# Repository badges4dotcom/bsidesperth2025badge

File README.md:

# BSides Perth 2025 Badge

## Physical Badge

Instructions on how to assemble the physical badge can be found [here](docs/AssemblyInstructions.md)

If a re-download of the physical badge is required, follow these [instructions](docs/DownloadInstructions.md). This will be required if you wish to attempt the online challenges (see Known Issues below).

### Parts List

| Qty | Item | Link | Alternative Link |
| --- | --- | --- | --- |
| 4	| 6x6x6mm Push Button Tactile Switch | [Link](https://a.aliexpress.com/_mtKEuoZ) || 
| 4	| 10k 1/4W 1% Metal Film Resistor | [Link](https://a.aliexpress.com/_m0tmaNF) ||
| 1	| 1x4 2.54mm Male Header Pin Connector | [Link](https://a.aliexpress.com/_mLn1ap7) ||
| 1	| 1x8 2.54mm Female Header Pin Connector | [Link](https://a.aliexpress.com/_mquvebf) | [Link](https://a.aliexpress.com/_mNltGYh) |
| 1	| 1x4 2.54mm Female Header Pin Connector | [Link](https://a.aliexpress.com/_mquvebf) | [Link](https://a.aliexpress.com/_mNltGYh) |
| 2	| 1x15 2.54mm Female Header Pin Connector | [Link](https://a.aliexpress.com/_mquvebf) | [Link](https://a.aliexpress.com/_mNltGYh) |
| 1	| 2x3 2.54mm Femal Header Pin Connector	| [Link](https://a.aliexpress.com/_mK6bxvJ) ||
| 1	| ESP32 DOIT DevKit v1 - 30Pin | [Link](https://a.aliexpress.com/_mr7LSPJ) ||
| 1	| 1.8" LCD TFT Display | [Link](https://a.aliexpress.com/_mPspKyp) ||

## Virtual Badge

The virtual badge can be accessed here: https://badge.bsidesperth.com.au/

The code for the Virtual Badge code can be found in this repository under "VirtualBadge".

The virtual badge does not support "Online Challenges", but does contain hidden features such as a second episode, cheats, and an easter egg.

The virtual badge now supports keyboard inputs. The four buttons are mapped to W [Up], S [Down], A [Left/A], and D [Right/B]. Once a keyboard input is used, the symbols used in the sequence game change to U = UP, D = DOWN, L = LEFT, R = RIGHT. Thanks again to Matt for the suggestion and the code snippet for this feature. 

## Physical Badge Code Template

There is a basic template for an Arduino program under the folder "Template". The template demonstrates basic use of the LCD screen, ESP32, and button inputs. The download instructions can be found [here](docs/DownloadInstructions.md).

## Virtual Badge Server (API for Online Challenges)

Code for the Virtual Badge Server (API for Online Challenges) will be made available ~1st November 2025.

## Badge Holder (3D Print)

A badge holder can be 3D printed using an off-the-shelf 3D printer. Recommended print settings are PLA plastic, 60+% infill, 40mm/s print speed. Some stringing may occur if filament is damp and/or print speed is too high.

## Customisation

Customisation of the virtual and physical badge are both possible. Extra details can be found [here](docs/Customisation.md)

## Known Issues

- To play the Online Challenges on a ESP32 supplied in a component pack, a re-download of the physical badge code to the ESP32 is required. [Fixed]
- Online Challenges were unavailable (18th Oct) due to firewall issue. This has since been resolved. [Fixed]
- Offline Challenges now generates sequences which use all four buttons (only three buttons were being used in the original code). [Fixed]

## Like the game/badge?

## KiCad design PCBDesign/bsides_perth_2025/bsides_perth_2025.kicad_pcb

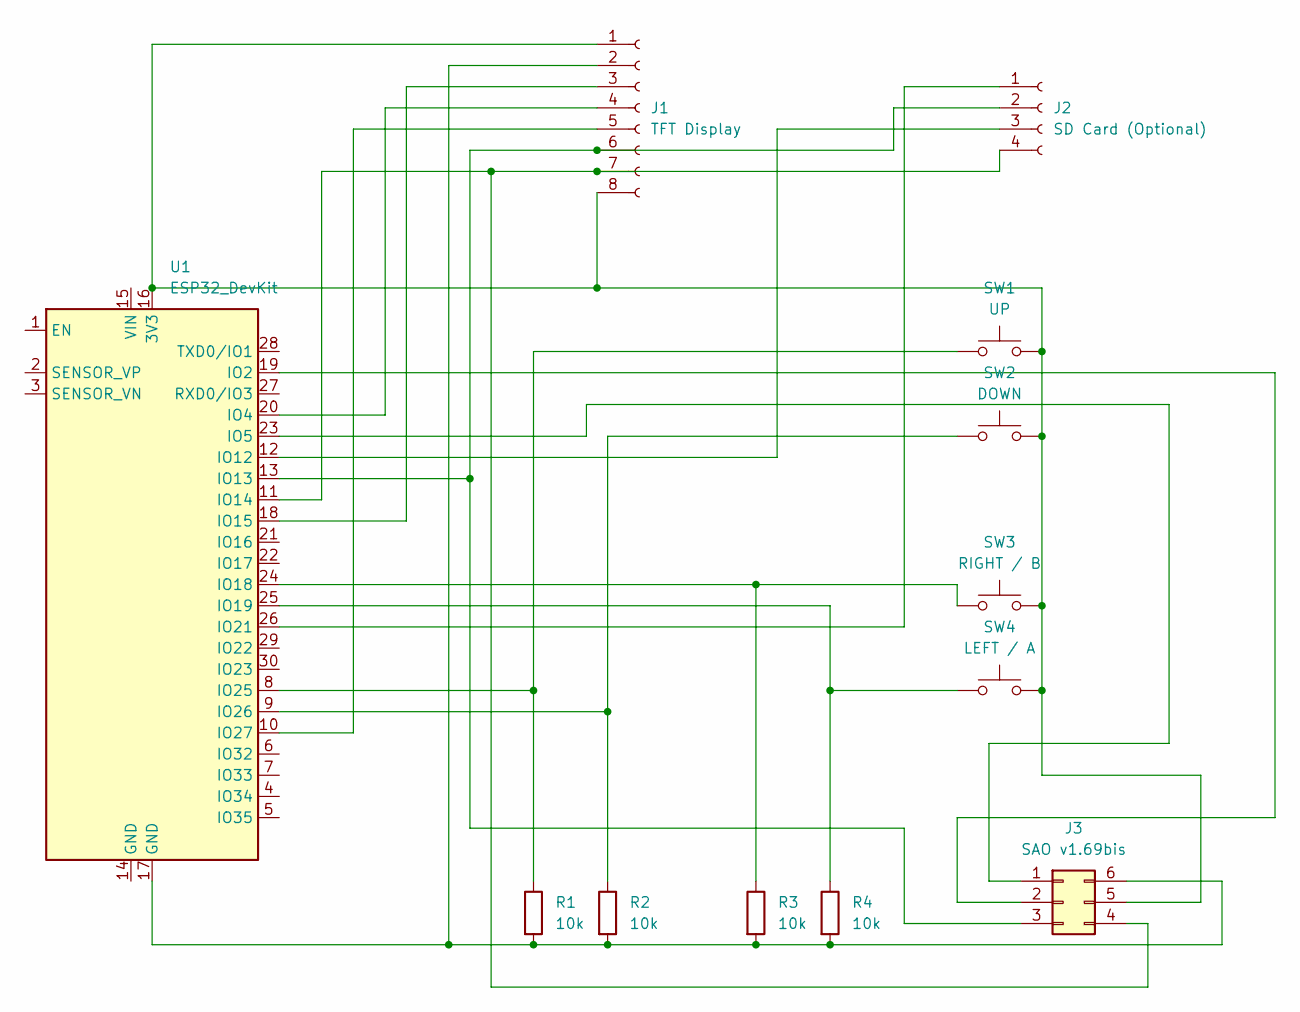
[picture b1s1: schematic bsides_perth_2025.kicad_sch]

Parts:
J1: TFT Display; PinHeader_1x08_P2.54mm_Vertical
J2: SD Card (Optional); PinHeader_1x04_P2.54mm_Vertical
J3: SAO v1.69bis; PinHeader_2x03_P2.54mm_Vertical
R1, R2, R3, R4: 10k; R_Axial_DIN0207_L6.3mm_D2.5mm_P10.16mm_Horizontal
SW1: UP; SW_PUSH_6mm_H5mm
SW2: DOWN; SW_PUSH_6mm_H5mm
SW3: RIGHT / B; SW_PUSH_6mm_H5mm
SW4: LEFT / A; SW_PUSH_6mm_H5mm
U1: ESP32_DevKit; esp32_devkit_v1_doit

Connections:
unnamed: J1.1, J1.8, J3.5, SW1.2, SW2.2, SW3.2, SW4.2, U1.16 (3V3)
unnamed: J1.2, J3.6, R1.2, R2.2, R3.2, R4.2, U1.17 (GND)
unnamed: J1.3, U1.18 (IO15)
unnamed: J1.4, U1.20 (IO4)
unnamed: J1.5, U1.10 (IO27)
unnamed: J1.6, J2.2, J3.3, U1.13 (IO13)
unnamed: J1.7, J2.4, J3.4, U1.11 (IO14)
unnamed: J2.1, U1.26 (IO21)
unnamed: J2.3, U1.12 (IO12)
unnamed: J3.1, U1.23 (IO5)
unnamed: J3.2, U1.19 (IO2)
unnamed: R1.1, SW1.1, U1.8 (IO25)
unnamed: R2.1, SW2.1, U1.9 (IO26)
unnamed: R3.1, SW3.1, U1.24 (IO18)
unnamed: R4.1, SW4.1, U1.25 (IO19)

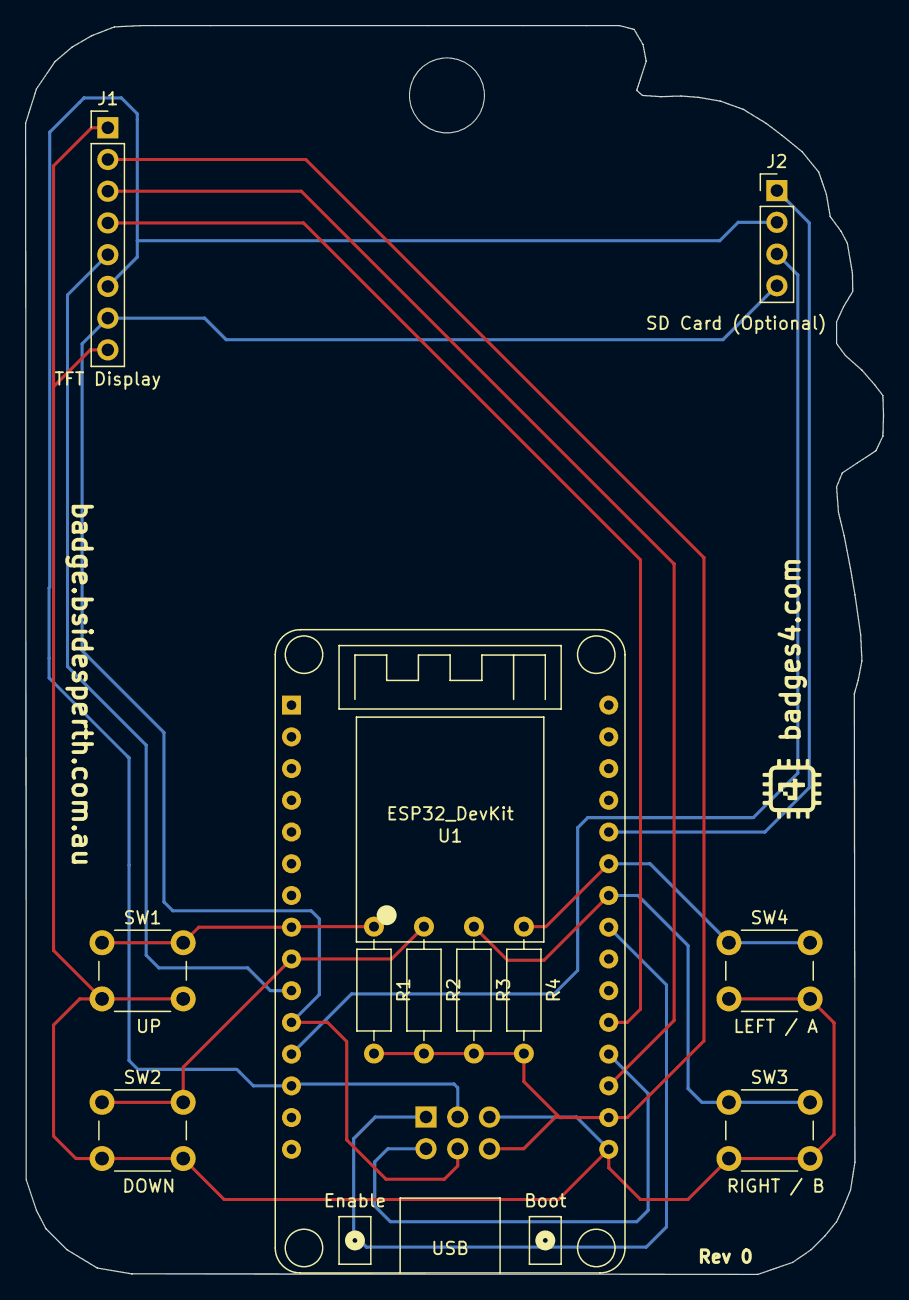
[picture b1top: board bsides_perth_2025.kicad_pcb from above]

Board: 2 copper layers, 68.7 x 100.0 mm, 12 parts (1 on the bottom side), 15 nets.

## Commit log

2025-10-17 Initial Upload of VirtualBadge
2025-10-17 Badge Holder - 3D Print
    Including the 3D Print for the Badge Holder
2025-10-17 Addition of the Physical Badge code
    Addition of the Physical Badge code
2025-10-17 Instructions and Gamemap
2025-10-17 Updated Assembly Instructions
2025-10-17 Minor finishing touches
2025-10-17 Last minute fixes
2025-10-18 Added parts list and minor fix
    Added parts list
    Improved Offline Challenge to use all four buttons for sequence
2025-10-19 Minor fixes, and keyboard support
    Minor fixes
    Keyboard Support
2025-10-20 Moved arduino project into directory named BSides so arduino ide does not complain
2025-10-20 Add github action to build binary for ESP32
2025-10-20 Allow build workflow to be run manually
2025-10-20 Fix github action
2025-10-20 Renamed directory "Images" to "images" so building works on linux
2025-10-20 Make the final binary file name simpler
2025-10-23 Badge Software Template + PCB Design
    Addition of:
    1) Badge Software Template
    2) PCB Design
